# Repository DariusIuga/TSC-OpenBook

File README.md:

# TSC-OpenBook

An implementation of an open-source E-book reader made in Autodesk Fusion 360.

## Block Diagram

## Enclosure

## PCB

## Display

## Descrierea Funcționalității Hardware

Acest proiect utilizează modulul **ESP32-C6-WROOM-1-N8** ca unitate principală de microcontroler (MCU). Acest modul dispune de un nucleu RISC-V pe 32 de biți ce rulează până la 160MHz, conectivitate Wi-Fi 6 și Bluetooth 5 (BLE) integrate, 512KB SRAM și interfațează cu 8MB de memorie flash NOR externă (W25Q64JV / W25Q512JVEIQ) prin SPI pentru stocarea firmware-ului.

**Componente Cheie și Interfețe:**

* **Afișaj:** Un display E-Paper (EPD) alb-negru de 7.5 inci, cu rezoluție 800x480 pixeli, este utilizat ca ieșire vizuală principală. Acesta se conectează la ESP32-C6 printr-o interfață SPI cu 4 fire, suplimentată de pini dedicați pentru reset (RST), selecție dată/comandă (DC), selecție cip (CS) și indicarea stării de ocupat (BUSY).
* **Managementul Alimentării:**
    * Dispozitivul este alimentat de o baterie Litiu-Polimer de 3.7V, 2500mAh.
    * Încărcarea bateriei este gestionată de circuitul integrat **MCP73831**, acceptând alimentare prin portul USB-C. Un LED de stare indică starea încărcării.
    * Circuitul integrat **MAX17048** acționează ca un indicator al nivelului bateriei (fuel gauge), monitorizând starea de încărcare a bateriei și comunicând această informație către MCU prin magistrala I2C.
    * Un regulator Low-Dropout (LDO) **XC6220A331MR-G** convertește tensiunea bateriei sau tensiunea USB (VBUS) la tensiunea stabilă de 3.3V necesară componentelor sistemului.
    * Un supervizor de tensiune **BD5229G-TR** monitorizează magistrala de 3.3V și menține ESP32-C6 în reset dacă tensiunea scade sub un prag sigur, asigurând stabilitatea sistemului.
* **Senzori de Mediu:** Un senzor **BME688** (sau BME680 conform BOM) este inclus pentru a măsura temperatura, umiditatea, presiunea barometrică și compușii organici volatili (VOC) pentru estimarea calității aerului. Acesta comunică cu ESP32-C6 prin magistrala I2C. *(Notă: Cerințele specifică BME688, BOM listează BME680. Funcționalitatea e similară, dar BME688 are capabilități AI îmbunătățite)*
* **Ceas de Timp Real (RTC):** Un modul RTC **DS3231SN** oferă măsurare precisă a timpului, chiar și atunci când MCU-ul principal este într-o stare de consum redus. Include un supercondensator de backup (**CPH3225A**) și comunică prin magistrala I2C.
* **Stocare:** Pe lângă memoria flash SPI externă pentru firmware (**W25Q512JVEIQ** - 64MByte), este prevăzut un slot pentru card MicroSD (**112A-TAAR-R03**) pentru stocarea datelor utilizatorului (ex. cărți electronice). Acesta interfațează cu ESP32-C6 folosind protocolul SDIO (sau SPI).
* **Interfață Utilizator:** Trei butoane tactile sunt disponibile pentru interacțiunea cu utilizatorul:
    * Buton Reset: Declanșează direct resetarea sistemului prin pinul EN (prin intermediul supervizorului de tensiune).
    * Buton Boot (GPIO0): Folosit pentru a plasa manual ESP32-C6 în modul de programare/bootloader la resetare.
    * Buton Change (GPIO21): Un buton de uz general pentru funcții specifice aplicației (ex. întoarcerea paginii, navigare în meniu).
* **Conectivitate & Depanare:**
    * Un port **USB-C** (**USB4110-GF-A**) oferă alimentare pentru încărcare și o interfață USB 2.0 Full-Speed pentru transfer de date și programare/depanare prin controlerul USB Serial/JTAG nativ al ESP32-C6. Protecție ESD (**USBLC6-2SC6Y**) este inclusă pe liniile USB.
    * Un conector **Qwiic/Stemma QT** (nepopulat în schemă, dar pinii I2C sunt disponibili pe J5) oferă o modalitate ușoară de a conecta periferice I2C suplimentare.
    * Pad-urile de test expun semnale cheie precum UART (TXD, RXD), SPI (pentru Flash și Card SD) și I2C în scopuri de depanare și testare.

## Utilizarea Pinilor ESP32-C6

Următorul tabel detaliază pinii GPIO specifici utilizați pe modulul ESP32-C6-WROOM-1 și funcțiile acestora în cadrul acestui proiect:

| Pin ESP32-C6 | Funcție                           | Component(e) Conectat(e)               | Interfață/Motiv                                              |
| :----------- | :-------------------------------- | :------------------------------------- | :----------------------------------------------------------- |
| GPIO0        | Selecție Boot / Intrare Buton     | SW_BOOT (Buton Boot), R_BOOT         | Pin standard pentru selecția modului boot; Intrare utilizator |
| GPIO1        | Ceas I2C                          | U4 (MAX17048), U3 (DS3231), SENSOR2 (BME68x), J5 (Qwiic) | Magistrală I2C comună (SCL) pentru multipli senzori/CI        |
| GPIO2        | Date I2C                          | U4 (MAX17048), U3 (DS3231), SENSOR2 (BME68x), J5 (Qwiic) | Magistrală I2C comună (SDA) pentru multipli senzori/CI        |
| GPIO3        | Selecție Cip E-Paper              | J1 (Header EPD)                        | Selecție Cip SPI (CS) pentru Afișajul E-Paper              |
| GPIO4        | Dată/Comandă E-Paper              | J1 (Header EPD)                        | Control Dată/Comandă (DC) pentru Afișajul E-Paper          |
| GPIO5        | Reset E-Paper                     | J1 (Header EPD)                        | Semnal Reset (RST) pentru Afișajul E-Paper               |
| GPIO6        | Stare Ocupat E-Paper              | J1 (Header EPD)                        | Semnal intrare Ocupat (Busy) de la Afișajul E-Paper          |
| GPIO7        | Hold Flash Extern                 | U1 (W25Q512JVEIQ), TP17                | Semnal SPI Hold (/HOLD) pentru memoria flash externă         |
| GPIO8        | Dată 0 Card SD                    | J2 (Slot Card SD), TP6                 | Linie Date SDIO 0 / SPI MISO                               |
| GPIO9        | Dată 1 Card SD                    | J2 (Slot Card SD), TP7                 | Linie Date SDIO 1                                          |
| GPIO10       | Comandă Card SD                   | J2 (Slot Card SD), TP5                 | Linie Comandă SDIO / SPI MOSI                              |
| GPIO11       | Ceas Card SD                      | J2 (Slot Card SD), TP4                 | Linie Ceas SDIO / SPI SCK                                  |
| GPIO12       | Protecție Scriere Flash Extern    | U1 (W25Q512JVEIQ), TP16                | Semnal SPI Protecție Scriere (/WP) pentru flash extern      |
| GPIO13       | MISO Flash Extern                 | U1 (W25Q512JVEIQ), TP15                | SPI Master In Slave Out (MISO) pentru flash extern         |
| GPIO14       | MOSI Flash Extern                 | U1 (W25Q512JVEIQ), TP14                | SPI Master Out Slave In (MOSI) pentru flash extern         |
| GPIO15       | Selecție Cip Flash Extern         | U1 (W25Q512JVEIQ), TP13                | Selecție Cip SPI (/CS) pentru memoria flash externă        |
| GPIO16       | UART TXD                          | TP12                                   | Date Transmise UART pentru depanare/programare             |
| GPIO17       | UART RXD                          | TP11                                   | Date Recepționate UART pentru depanare/programare          |
| GPIO18       | Ceas Flash Extern                 | U1 (W25Q512JVEIQ), TP3                 | Ceas SPI (SCK) pentru memoria flash externă                |
| GPIO19       | Dată 2 Card SD                    | J2 (Slot Card SD), TP8                 | Linie Date SDIO 2                                          |
| GPIO20       | Dată 3 Card SD / Detectare Card   | J2 (Slot Card SD), TP9                 | Linie Date SDIO 3 / Intrare Detectare Card                 |
| GPIO21       | Intrare Buton Change              | SW_CHANGE (Buton Change)               | Intrare de Uz General pentru interacțiune utilizator         |
| USB_D-       | Date Negative USB                 | J4 (Conector USB-C)                    | Semnal Nativ USB D-                                        |
| USB_D+       | Date Pozitive USB                 | J4 (Conector USB-C)                    | Semnal Nativ USB D+                                        |
| EN           | Activare Sistem / Reset           | U5 (BD5229G), SW_RESET (Buton Reset)   | Activare Cip, controlat de supervizor tensiune/buton       |

*Notă: Perifericele SPI partajate (cum ar fi afișajul E-Paper și potențial cardul SD în modul SPI) ar partaja în mod tipic liniile SCK, MOSI și MISO, necesitând pini CS dedicați pentru fiecare dispozitiv. Cu toate acestea, acest design folosește GPIO-uri separate pentru controlul EPD și interfețe dedicate (SDIO și SPI) pentru Cardul SD și respectiv Flash-ul Extern, conform mapării de mai sus.*

## Pași de Implementare

Procesul de dezvoltare a acestui proiect a urmat, în linii mari, următorii pași:

1.  **Analiza Cerințelor:** Înțelegerea documentelor de specificații (MRD, PRD, ERD) și a cerințelor hardware detaliate.
2.  **Selecția Componentelor:** Alegerea componentelor principale (ESP32-C6, display E-Paper 7.5", BME68x, MAX17048, MCP73831, DS3231SN, W25Q512JVEIQ etc.) pe baza cerințelor de funcționalitate, performanță, consum și cost.
3.  **Proiectarea Schematicii:** Crearea diagramelor electrice în Autodesk Fusion 360, interconectând componentele conform datasheet-urilor și logicii funcționale.
4.  **Design PCB (Layout):** Amplasarea componentelor pe placa de circuit imprimat, rutarea traseelor electrice respectând constrângerile (grosimi trasee de putere/semnal, izolare, reguli DRC/ERC).
5.  **Verificări Design:** Rularea verificărilor ERC (Electrical Rule Check) și DRC (Design Rule Check) pentru a identifica potențiale probleme în schematică și layout.
6.  **Modelare 3D și Integrare Mecanică:** Crearea modelelor 3D pentru PCB-ul asamblat, baterie și display. Integrarea acestora în modelul 3D al carcasei furnizate pentru a verifica potrivirea mecanică și spațiul disponibil.
7.  **Generare Fișiere de Producție:** Crearea fișierelor Gerber pentru fabricarea PCB-ului, a listei de materiale (BOM - Bill of Materials) și a fișierului Pick and Place (CPL) pentru asamblarea automată.

## Estimare Consum Energie

Consumul de energie al dispozitivului variază semnificativ în funcție de modul de operare. Mai jos sunt estimări aproximative:

* **Mod Activ (Citire / Conectat Wi-Fi):**
    * ESP32-C6: ~80-150mA (poate crește semnificativ în timpul transmisiei active Wi-Fi/BT)
    * Display E-Paper: Neglijabil (µA) când imaginea este statică.
    * Senzori, RTC, Flash (citire ocazională): ~5-10mA în total.
    * **Total estimat:** **~90 - 170 mA** (fără refresh EPD)

* **Mod Refresh Display E-Paper:**
    * Display-ul consumă curent doar în timpul actualizării (aproximativ 1-2 secunde).
    * Consum EPD în refresh: ~20-40mA.
    * **Total estimat (în timpul refresh-ului):** Consumul modului activ + **~20-40mA**.

* **Mod Sleep (Deep Sleep):**
    * ESP32-C6: țintă < 50µA (tipic 10-25µA în deep sleep).
    * RTC (pe backup): ~1-2µA.
    * Fuel Gauge (MAX17048): ~5-10µA.
    * LDO (Quiescent current): ~1-5µA.
    * Scurgeri diverse: ~1-5µA.
    * **Total estimat:** **~20 - 50 µA**. Acest consum redus permite o durată de viață a bateriei foarte lungă în standby.

**Notă:** Aceste valori sunt estimative și depind în mare măsură de implementarea firmware și de caracteristicile specifice ale componentelor utilizate. 

## Considerente Design și Amplasare

**Selecția Componentelor:**

Alegerea componentelor s-a bazat pe cerințele hardware specificate, urmărind un echilibru între funcționalitate, consum redus de energie, disponibilitate și cost:

* **ESP32-C6:** Selectat pentru capabilitățile sale moderne Wi-Fi 6/BLE, nucleul RISC-V eficient energetic, suportul bun pentru moduri low-power și setul adecvat de periferice (SPI, I2C, SDIO, USB).
* **Display E-Paper 7.5":** Ideal pentru un e-reader datorită consumului zero în stare statică și lizibilității excelente în lumină ambientală. Interfața SPI este comună și ușor de implementat.
* **BME680/688:** Integrarea senzorilor de mediu într-un singur pachet compact (I2C).
* **MCP73831 & MAX17048:** O combinație standard și fiabilă pentru încărcarea și monitorizarea precisă a bateriei Li-Po.
* **DS3231SN:** Un RTC precis cu compensare de temperatură, esențial pentru funcții dependente de timp. Supercapacitorul elimină necesitatea unei baterii de backup separate pentru RTC.
* **W25Q512JVEIQ:** Oferă cei 8MB (64Mbit) de stocare flash externă necesari conform specificațiilor, folosind o interfață SPI standard.
* **Conectori (USB-C, SD Card, FFC):** Aleși pentru a corespunde standardelor actuale și cerințelor de conectivitate.

**Amplasarea Componentelor și Integrarea în Carcasă:**

Layout-ul PCB-ului și amplasarea componentelor au fost realizate ținând cont de constrângerile carcasei și de regulile de bună practică în designul electronic:

* **Potrivire Mecanică:** Forma PCB-ului a fost adaptată pentru a se potrivi în interiorul carcasei și a utiliza punctele de montaj existente.
* **Antena RF:** Modulul ESP32-C6 a fost plasat la marginea PCB-ului, cu antena orientată spre exterior. Zona de sub antenă a fost decupată din PCB și nu conține plan de masă sau trasee, conform recomandărilor Espressif, pentru a maximiza performanța radio.
* **Conectori Externi:** Portul USB-C și butoanele au fost poziționate pentru a corespunde decupajelor din carcasă.
* **Conector Display:** Conectorul FFC pentru display a fost plasat strategic pentru a facilita conectarea cablului flexibil al E-Paper-ului.
* **Amplasare Generală:** Componentele au fost plasate exclusiv pe stratul TOP, conform cerințelor. S-a urmărit o distribuție logică (ex: circuitul de încărcare lângă USB, senzorii grupați, memoria flash lângă MCU).
* **Condensatoare de Decuplare:** Au fost plasate cât mai aproape posibil de pinii de alimentare ai circuitelor integrate (ESP32, BME68x, MAX17048 etc.) pentru a asigura stabilitatea alimentării.
* **Baterie:** Spațiul principal din interiorul carcasei a fost alocat pentru bateria Li-Po, care se conectează direct la pad-uri de pe PCB.

## Bill of Materials (BOM)

| Component | Description | Datasheet | Shop - Mouser |
|-----------|-------------|-----------|------|
| ESP32-C6-WROOM-1-N8 | Wi-Fi, BLE, Zigbee SoC Module | [Datasheet](https://www.espressif.com/sites/default/files/documentation/esp32-c6-wroom-1_wroom-1u_datasheet_en.pdf) | [Shop](https://eu.mouser.com/ProductDetail/Espressif-Systems/ESP32-C6-WROOM-1U-N8?qs=1Kr7Jg1SGW%2FzPU4G%252ByMwkA%3D%3D) |
| MCP73831 | Li-Po Battery Charging Controller | [Datasheet](https://eu.mouser.com/datasheet/2/268/MCP73831_Family_Data_Sheet_DS20001984H-3441711.pdf) | [Shop](https://eu.mouser.com/ProductDetail/Microchip-Technology/MCP73831T-2ACI-OT?qs=yUQqVecv4qvbBQBGbHx0Mw%3D%3D) |
| XC6220A331MR-G | LDO Voltage Regulator | [Datasheet](https://eu.mouser.com/datasheet/2/760/xc6220-3371556.pdf) | [Shop](https://eu.mouser.com/ProductDetail/Torex-Semiconductor/XC6220A331MR-G?qs=AsjdqWjXhJ8ZSWznL1J0gg%3D%3D) |
| BME680 | Environmental Sensor | [Datasheet](https://eu.mouser.com/datasheet/2/783/BST_BME680_DS001-1509608.pdf) | [Shop](https://eu.mouser.com/ProductDetail/Bosch-Sensortec/BME680?qs=v271MhAjFHjo0yA%2FC4OnDQ%3D%3D) |
| DS3231SN | Real-Time Clock | [Datasheet](https://eu.mouser.com/datasheet/2/609/DS3231-3421123.pdf) | [Shop](https://eu.mouser.com/ProductDetail/Analog-Devices-Maxim-Integrated/DS3231SN?qs=1eQvB6Dk1vhUlr8%2FOrV0Fw%3D%3D) |
| W25Q512JVEIQ | 512Mb (64MB) Flash Memory | [Datasheet](https://eu.mouser.com/datasheet/2/949/Winbond_W25Q512JV_Datasheet-3240039.pdf) | [Shop](https://eu.mouser.com/ProductDetail/Winbond/W25Q512JVEIQ?qs=l7cgNqFNU1jw6svr3at6tA%3D%3D) |
| MAX17048G+T10 | Battery Fuel Gauge | [Datasheet](https://eu.mouser.com/datasheet/2/609/MAX17048_MAX17049-3469099.pdf) | [Shop](https://eu.mouser.com/ProductDetail/Analog-Devices-Maxim-Integrated/MAX17048G%2bT10?qs=D7PJwyCwLAoGnnn8jEPRBQ%3D%3D) |
| SI1308EDL-T1-GE3 | N-Channel MOSFET | [Datasheet](https://www.vishay.com/docs/63399/si1308edl.pdf) | [Shop](https://eu.mouser.com/ProductDetail/Vishay-Semiconductors/SI1308EDL-T1-GE3?qs=bX1%252BNvsK%2FBramh9tgpOaEw%3D%3D) |
| DMG2305UX-7 | P-Channel MOSFET | [Datasheet](https://www.diodes.com/assets/Datasheets/DMG2305UX.pdf) | [Shop](https://eu.mouser.com/ProductDetail/Diodes-Incorporated/DMG2305UX-7?qs=L1DZKBg7t5F%2FNBHrjfxC%252Bg%3D%3D) |
| USBLC6-2SC6Y | USB ESD Protection | [Datasheet](https://eu.mouser.com/datasheet/2/389/usblc6_2sc6y-1852505.pdf) | [Shop](https://eu.mouser.com/ProductDetail/STMicroelectronics/USBLC6-2SC6Y?qs=gNDSiZmRJS%2FOgDexvXkdow%3D%3D) |
| USB4110-GF-A | USB Type-C Connector | [Datasheet](https://eu.mouser.com/datasheet/2/837/GCT_USB4110_Product_Drawing___20k_cycles-3455479.pdf) | [Shop](https://eu.mouser.com/ProductDetail/GCT/USB4110-GF-A?qs=KUoIvG%2F9IlYiZvIXQjyJeA%3D%3D) |
| 112A-TAAR-R03 | Micro SD Card Connector | [Datasheet](https://www.attend.com.tw/data/download/file/112A-TAAR-R03_Spec.pdf) | [Shop](https://www.tme.eu/ro/details/mcc-sdmicro/conectori-pentru-cartele/attend/112a-taar-r03/) |
| Waveshare Display | 7.5" E-Ink | [Datasheet](https://files.waveshare.com/upload/6/60/7.5inch_e-Paper_V2_Specification.pdf) | [Shop](https://www.waveshare.com/7.5inch-e-paper-hat.htm) |
| CPH3225A | 11mF Supercapacitor | [Datasheet](https://eu.mouser.com/datasheet/2/360/Seiko_Instruments_MicroBattery_E_20230330_2024Jan_-3561061.pdf) | [Shop](https://eu.mouser.com/ProductDetail/Seiko-Semiconductors/CPH3225A?qs=3etwrb1wR%252BhUOph6lAO7eg%3D%3D) |
| BD5229G-TR | Voltage Supervisor | [Datasheet](https://eu.mouser.com/datasheet/2/348/bd52xxg_e-3421856.pdf) | [Shop](https://eu.mouser.com/ProductDetail/ROHM-Semiconductor/BD5229G-TR?qs=PVQ7ZECv46n5JbI7K86q0w%3D%3D) |

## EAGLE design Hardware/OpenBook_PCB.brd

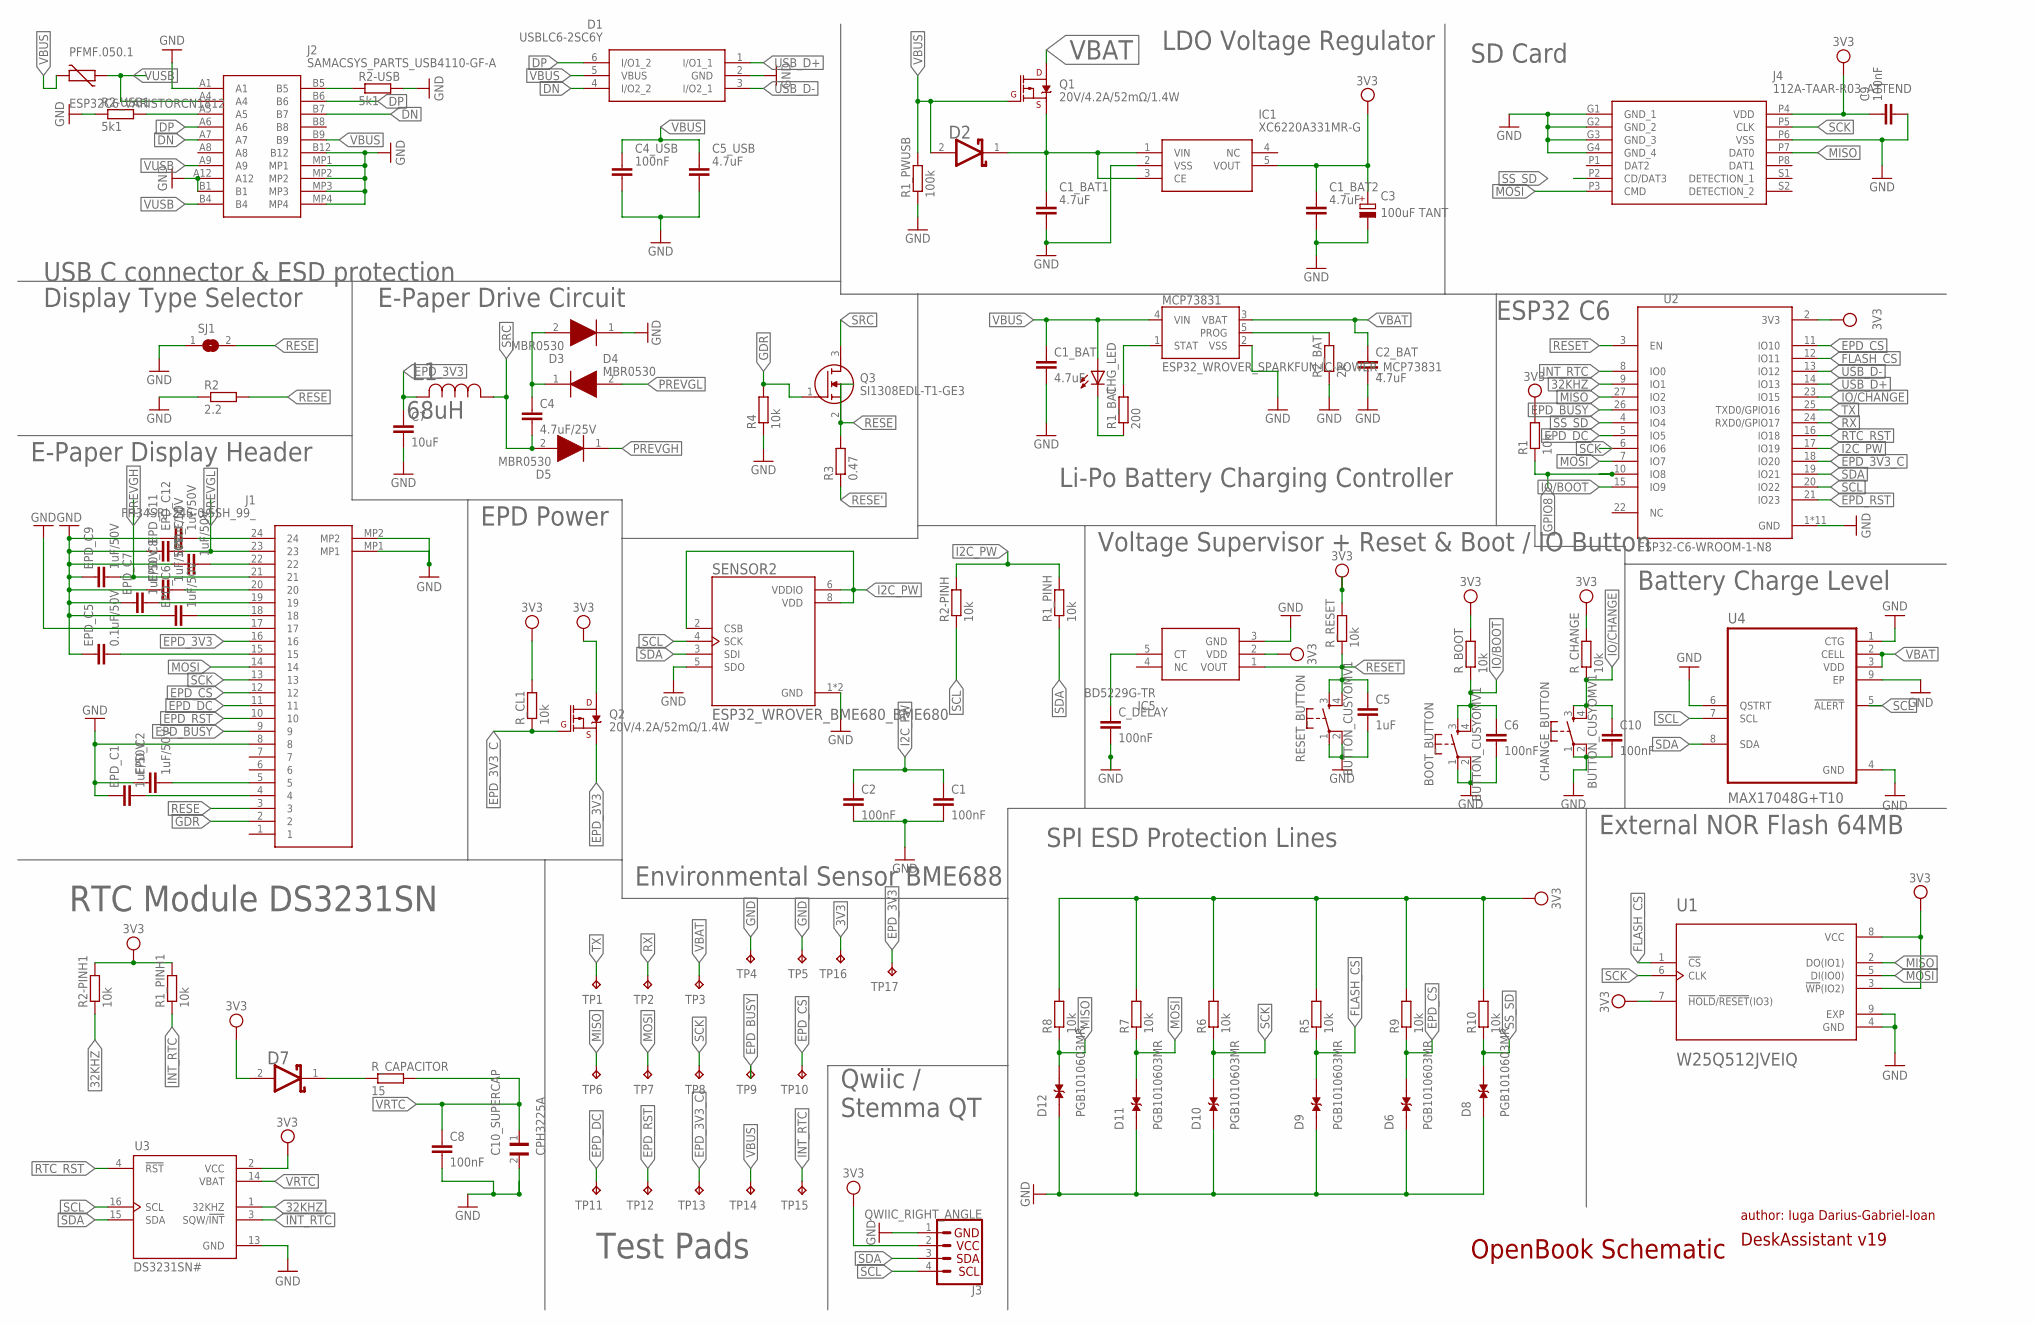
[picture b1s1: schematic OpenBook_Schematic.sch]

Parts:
BOOT_BUTTON: BUTTON_CUSYOMV1; MYBUTTON
C1, C2, C6, C10: 100nF; ESP32_WROVER_EAGLE-LTSPICE_C0402
C1_BAT, C2_BAT: 4.7uF; ESP32_WROVER_EAGLE-LTSPICE_C0402
C1_BAT1, C5_USB: 4.7uF; CAPC1005X60
C1_BAT2: 4.7uF; CAPM3216X180
C3: 100uF TANT; CAPMP3216X180N
C4: 4.7uF/25V; EAGLE-LTSPICE_C0402
C4_USB, C9: 100nF; CAPC1005X60
C5: 1uF; ESP32_WROVER_EAGLE-LTSPICE_C0402
C7: 10uF; EAGLE-LTSPICE_C0402
C8: 100nF; EAGLE-LTSPICE_C0402
C10_SUPERCAP: CPH3225A; CAPCP3225X100N
CHANGE_BUTTON: BUTTON_CUSYOMV1; MYBUTTON
CHG_LED: ADAFRUIT_LEDCHIP-LED0603; ADAFRUIT_CHIP-LED0603
C_DELAY: 100nF; ESP32_WROVER_EAGLE-LTSPICE_C0402
D1: USBLC6-2SC6Y; SOT95P280X145-6N
D2, D7: ESP32_WROVER_AVX---SD0805S020S1R0_AVX_SD0805S020S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; ESP32_WROVER_AVX---SD0805S020S1R0_AVX_SD0805S020S1R0_0
D3, D4, D5: MBR0530; SOD3716X135N
D6, D8, D9, D10, D11, D12: PGB1010603MR; DIOC1608X36N
EPD_C1, EPD_C2, EPD_C6, EPD_C7, EPD_C8, EPD_C9, EPD_C10, EPD_C11, EPD_C12: 1uF/50V; ESP32_WROVER_EAGLE-LTSPICE_C0402
EPD_C5: 0.1uF/50V; ESP32_WROVER_EAGLE-LTSPICE_C0402
IC1: XC6220A331MR-G; SOT95P280X120-5N
IC5: BD5229G-TR; SOT95P280X125-5N
J1: FH34SRJ-24S-0.5SH_99_; FH34SRJ24S05SH99
J2: SAMACSYS_PARTS_USB4110-GF-A; SAMACSYS_PARTS_USB4110GFA
J3: QWIIC_RIGHT_ANGLE; JST04_1MM_RA
J4: 112A-TAAR-R03_ATTEND; 112ATAARR03ATTEND
L1: 68uH; IND_4828-WE-TPC_WRE
MCP73831: ESP32_WROVER_SPARKFUN-IC-POWER_MCP73831; ESP32_WROVER_SPARKFUN-IC-POWER_SOT23-5
PFMF.050.1: ESP32C6_VARISTORCN1812; ESP32C6_VARISTOR_CT/CN1812
Q1, Q2: 20V/4.2A/52mΩ/1.4W; ESP32_WROVER_SPARKFUN-DISCRETESEMI_SOT23-3
Q3: SI1308EDL-T1-GE3; SOT65P210X110-3N
R1, R1_PINH, R1_PINH1, R2-PINH, R2-PINH1, R4, R5, R6, R7, R8, R9, R10: 10k; ESP32_WROVER_EAGLE-LTSPICE_R0402
R1_BAT: 200; ESP32_WROVER_EAGLE-LTSPICE_R0402
R1_PWUSB: 100k; ESP32_WROVER_EAGLE-LTSPICE_R0402
R2: 2.2; ESP32_WROVER_EAGLE-LTSPICE_R0402
R2-USB, R2-USB1: 5k1; ESP32_WROVER_EAGLE-LTSPICE_R0402
R2_BAT: 2k; ESP32_WROVER_EAGLE-LTSPICE_R0402
R3: 0.47; ESP32_WROVER_EAGLE-LTSPICE_R0402
RESET_BUTTON: BUTTON_CUSYOMV1; MYBUTTON
R_BOOT: 10k; ESP32_WROVER_EAGLE-LTSPICE_R0402
R_CAPACITOR: 15; ESP32_WROVER_EAGLE-LTSPICE_R0402
R_CHANGE: 10k; ESP32_WROVER_EAGLE-LTSPICE_R0402
R_CL1: 10k; ESP32_WROVER_EAGLE-LTSPICE_R0402
R_RESET: 10k; ESP32_WROVER_EAGLE-LTSPICE_R0402
SENSOR2: ESP32_WROVER_BME680_BME680; ESP32_WROVER_BME680_PSON80P300X300X100-8N
SJ1: SJ
TP1, TP2, TP3, TP4, TP5, TP6, TP7, TP8, TP9, TP10, TP11, TP12, TP13, TP14, TP15, TP16, TP17: TPB1,27; B1,27
U1: W25Q512JVEIQ; SON127P600X800X80-9N
U2: ESP32-C6-WROOM-1-N8; XCVR_ESP32-C6-WROOM-1-N8
U3: DS3231SN#; SOIC127P1032X265-16N
U4: MAX17048G+T10; SON50P200X200X80-9N

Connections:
3V3: C1_BAT2.1, C3.1 (+), C9.1, D7.2 (ANODE), IC1.5 (VOUT), IC5.2 (VDD), J3.2, J4.P4 (VDD), Q2.3 (D), R1.2, R1_PINH1.2, R2-PINH1.2, R5.2, R6.2, R7.2, R8.2, R9.2, R10.2, R_BOOT.2, R_CHANGE.2, R_CL1.2, R_RESET.2, TP16.TP, U1.3 (!WP!(IO2)), U1.7 (!HOLD!/!RESET!(IO3)), U1.8 (VCC), U2.2 (3V3), U3.2 (VCC)
32KHZ: R2-PINH1.1, U2.9 (IO1), U3.1 (32KHZ)
DN: D1.4 (I/O2_2), J2.A7, J2.B7
DP: D1.6 (I/O1_2), J2.A6, J2.B6
EPD_3V3: C7.1, J1.16, L1.2, Q2.2 (S), TP17.TP
EPD_3V3_C: Q2.1 (G), R_CL1.1, TP13.TP, U2.18 (IO20)
EPD_BUSY: J1.9, TP9.TP, U2.26 (IO3)
EPD_CS: D6.2, J1.12, R9.1, TP10.TP, U2.11 (IO10)
EPD_DC: J1.11, TP11.TP, U2.5 (IO5)
EPD_RST: J1.10, TP12.TP, U2.21 (IO23)
FLASH_CS: D9.2, R5.1, U1.1 (!CS), U2.12 (IO11)
GDR: J1.2, Q3.1 (G), R4.2
GND: BOOT_BUTTON.1, BOOT_BUTTON.2, C1.2, C1_BAT.2, C1_BAT1.2, C1_BAT2.2, C2.2, C2_BAT.2, C3.2 (-), C4_USB.2, C5.2, C5_USB.2, C6.2, C7.2, C8.2, C9.2, C10.2, C10_SUPERCAP.2, CHANGE_BUTTON.1, CHANGE_BUTTON.2, C_DELAY.2, D1.2 (GND), D3.1 (K), D6.1, D8.1, D9.1, D10.1, D11.1, D12.1, EPD_C1.1, EPD_C2.1, EPD_C5.1, EPD_C6.1, EPD_C7.1, EPD_C8.1, EPD_C9.1, EPD_C10.1, EPD_C11.1, EPD_C12.1, IC1.2 (VSS), IC5.3 (GND), J1.8, J1.17, J1.MP1, J1.MP2, J2.A1, J2.A12, J2.B1, J2.B12, J2.MP1, J2.MP2, J2.MP3, J2.MP4, J3.1, J4.G1 (GND_1), J4.G2 (GND_2), J4.G3 (GND_3), J4.G4 (GND_4), J4.P6 (VSS), MCP73831.2 (VSS), R1_PWUSB.1, R2.1, R2-USB.2, R2-USB1.1, R2_BAT.1, R4.1, RESET_BUTTON.1, RESET_BUTTON.2, SENSOR2.1 (GND), SENSOR2.5 (SDO), SENSOR2.7 (GND), SJ1.1, TP4.TP, TP5.TP, U1.4 (GND), U1.9 (EXP), U2.1 (GND), U2.28 (GND), U2.29_1 (GND), U2.29_2 (GND), U2.29_3 (GND), U2.29_4 (GND), U2.29_5 (GND), U2.29_6 (GND), U2.29_7 (GND), U2.29_8 (GND), U2.29_9 (GND), U3.13 (GND), U4.1 (CTG), U4.4 (GND), U4.6 (QSTRT), U4.9 (EP)
GPIO8: R1.1, U2.10 (IO8)
I2C_PW: C1.1, C2.1, R1_PINH.2, R2-PINH.2, SENSOR2.2 (CSB), SENSOR2.6 (VDDIO), SENSOR2.8 (VDD), U2.17 (IO19)
INT_RTC: R1_PINH1.1, TP15.TP, U2.8 (IO0), U3.3 (SQW/!INT)
IO/BOOT: BOOT_BUTTON.3, BOOT_BUTTON.4, C6.1, R_BOOT.1, U2.15 (IO9)
IO/CHANGE: C10.1, CHANGE_BUTTON.3, CHANGE_BUTTON.4, R_CHANGE.1, U2.23 (IO15)
MISO: D12.2, J4.P7 (DAT0), R8.1, TP6.TP, U1.2 (DO(IO1)), U2.27 (IO2)
MOSI: D11.2, J1.14, J4.P3 (CMD), R7.1, TP7.TP, U1.5 (DI(IO0)), U2.7 (IO7)
unnamed: C1_BAT1.1, D2.1 (CATHODE), IC1.1 (VIN), IC1.3 (CE), Q1.2 (S)
unnamed: J2.A5, R2-USB1.2
unnamed: C4.1, D3.2 (A), D4.1 (K)
unnamed: MCP73831.5 (PROG), R2_BAT.2
unnamed: MCP73831.1 (STAT), R1_BAT.2
unnamed: CHG_LED.C, R1_BAT.1
unnamed: EPD_C1.2, J1.4
unnamed: EPD_C2.2, J1.5
unnamed: EPD_C5.2, J1.15
unnamed: EPD_C6.2, J1.18
unnamed: EPD_C7.2, J1.19
unnamed: EPD_C8.2, J1.20
unnamed: C_DELAY.1, IC5.5 (CT)
unnamed: EPD_C10.2, J1.22
unnamed: D7.1 (CATHODE), R_CAPACITOR.1
unnamed: EPD_C12.2, J1.24
unnamed: J2.B5, R2-USB.1
PREVGH: D5.1 (K), EPD_C9.2, J1.21
PREVGL: D4.2 (A), EPD_C11.2, J1.23
RESE: J1.3, Q3.2 (S), R2.2, R3.2, SJ1.2
RESE': R3.1
RESET: C5.1, IC5.1 (VOUT), RESET_BUTTON.3, RESET_BUTTON.4, R_RESET.1, U2.3 (EN)
RTC_RST: U2.16 (IO18), U3.4 (!RST)
RX: TP2.TP, U2.24 (RXD0/GPIO17)
SCK: D10.2, J1.13, J4.P5 (CLK), R6.1, TP8.TP, U1.6 (CLK), U2.6 (IO6)
SCL: J3.4, R2-PINH.1, SENSOR2.4 (SCK), U2.20 (IO22), U3.16 (SCL), U4.5 (!ALERT), U4.7 (SCL)
SDA: J3.3, R1_PINH.1, SENSOR2.3 (SDI), U2.19 (IO21), U3.15 (SDA), U4.8 (SDA)
SRC: C4.2, D5.2 (A), L1.1, Q3.3 (D)
SS_SD: D8.2, J4.P2 (CD/DAT3), R10.1, U2.4 (IO4)
TX: TP1.TP, U2.25 (TXD0/GPIO16)
USB_D+: D1.1 (I/O1_1), U2.14 (IO13)
USB_D-: D1.3 (I/O2_1), U2.13 (IO12)
VBAT: C2_BAT.1, MCP73831.3 (VBAT), Q1.3 (D), TP3.TP, U4.2 (CELL), U4.3 (VDD)
VBUS: C1_BAT.1, C4_USB.1, C5_USB.1, CHG_LED.A, D1.5 (VBUS), D2.2 (ANODE), J2.B9, MCP73831.4 (VIN), PFMF.050.1.2, Q1.1 (G), R1_PWUSB.2, TP14.TP
VRTC: C8.1, C10_SUPERCAP.1, R_CAPACITOR.2, U3.14 (VBAT)
VUSB: J2.A4, J2.A9, J2.B4, PFMF.050.1.1

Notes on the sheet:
SD Card
USB C connector & ESD protection
LDO Voltage Regulator
ESP32 C6
Li-Po Battery Charging Controller
E-Paper Drive Circuit
Display Type Selector
E-Paper Display Header
EPD Power
Environmental Sensor BME688
Voltage Supervisor + Reset & Boot / IO Button
Battery Charge Level
External NOR Flash 64MB
SPI ESD Protection Lines
Qwiic / Stemma QT
Test Pads
RTC Module DS3231SN
OpenBook Schematic
author: Iuga Darius-Gabriel-Ioan
DeskAssistant v19

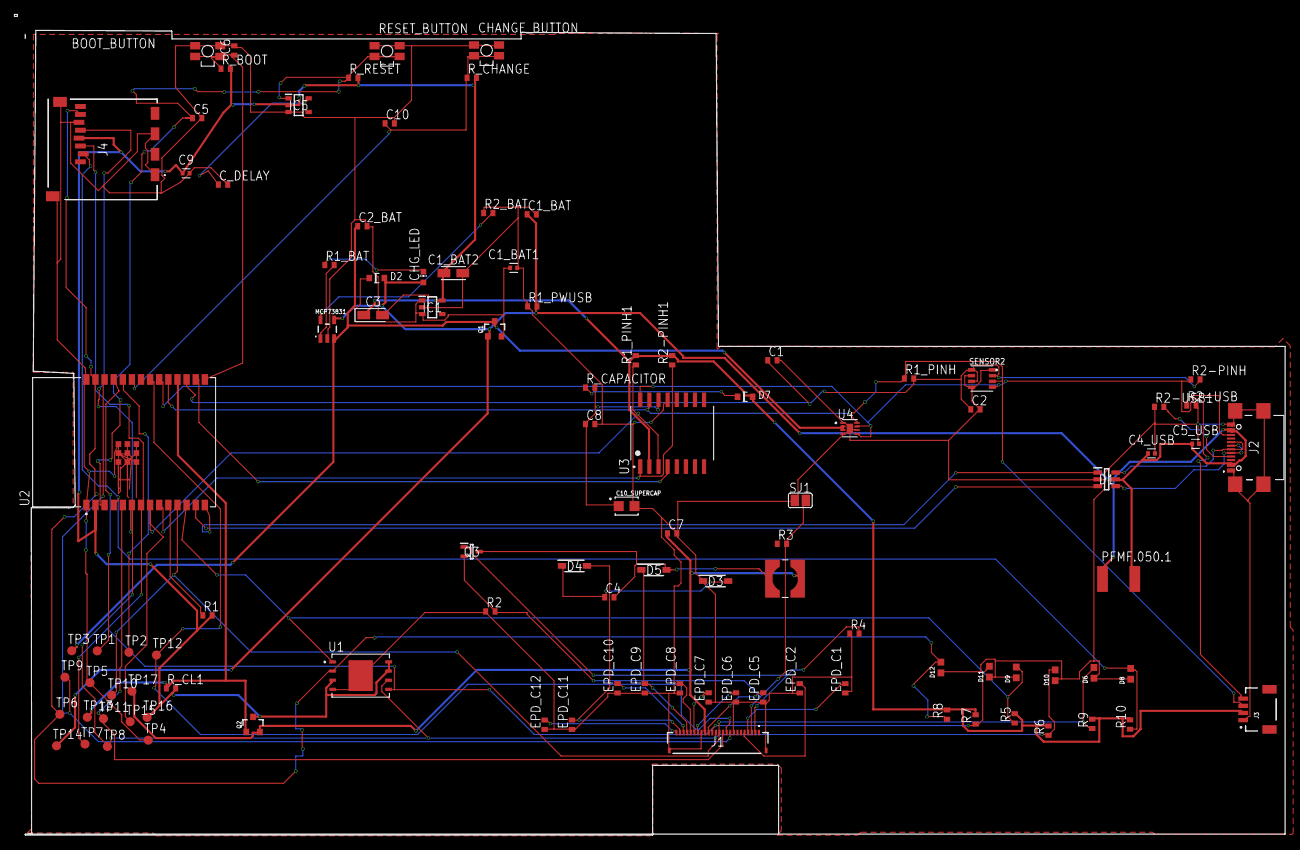
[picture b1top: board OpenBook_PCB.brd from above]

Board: 2 copper layers, 177.1 x 114.4 mm, 103 parts (0 on the bottom side), 55 nets.

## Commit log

2025-04-06 Add electronics files
2025-04-06 Add images to readme
2025-04-06 Add block diagram
2025-04-06 Fix png extensions
2025-04-06 Am adaugat descrierea hardware si a functionalitatii pin-urilor
2025-04-06 Add bom to readme
2025-04-06 Add exploded view
2025-04-06 Removed old 3D archive
2025-04-14 Improve readme (fixes #1)
2025-04-14 Fix schematic warnings (fixes #2, fixes #3, fixes #4, fixes #5)
2025-04-14 Moved PCB dimensions from layer Top to layer Dimensions (fixes #8)
2025-04-14 Adjusted components so the pins are on top of the SMD pads (fixes #6)
2025-04-15 Added cutout for PCB near buttons (fixes #7)

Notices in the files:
parts and their libraries:
COPYRIGHT: Copyright (C) 2024 Ultra Librarian. All rights reserved.
